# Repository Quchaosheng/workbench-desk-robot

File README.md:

# Workbench Desk Robot

> **Verify before you say done.**
>
> An evidence-first foundation for mobile domestic robots: bounded actions,
> replayable events, and a verifier that can say **confirmed**, **refuted**, or
> **insufficient evidence**.

[简体中文](README.zh-CN.md) · [Interactive 3D view](docs/assets/premium-product-render.html)

## Why Workbench?

Robot demos often treat “command accepted” as “task complete”. Workbench keeps
the proof in the loop:

```text
goal -> bounded planner -> semantic action -> trusted executor
                                      \-> event store -> verifier -> replay/dashboard
```

| Layer | Responsibility |
| --- | --- |
| Intent | Select from a small, typed action vocabulary |
| Execution | Dispatch through trusted runtime code |
| Verification | Check post-action evidence; never guess success |
| Replay | Rebuild the state from an append-only event stream |

## Quickstart

Requirements: Python 3.12. No GPU is required for the offline runtime.

```bash
git clone https://github.com/Quchaosheng/workbench-desk-robot.git
cd workbench-desk-robot
python -m pip install -e ".[dev]"
python tools/scripts/sim_cli.py doctor
python tools/scripts/sim_cli.py run normal-001 --runner scripted --output-dir runs/demo
```

Run the full portable checks:

```bash
python -m pytest -q
python -m ruff check .
```

The scripted runner writes a replayable artifact (manifest, scene, events,
logs, metadata, and SHA-256 checksums) labelled `SCRIPTED_FIXTURE`.

## What is included

- Evidence-first verification with `confirmed`, `refuted`, and `insufficient_evidence`.
- Strict JSON schemas and matching Pydantic contracts.
- Append-only SQLite event storage with integrity-checked replay.
- Fail-closed policy validation for bounded semantic tools.
- Read-only dashboard and deterministic simulation fixtures.
- Software-only foundations for MCU, CAN, Motion, and BSP boundaries.

## Optional: OmniLink knowledge layer

[OmniLink AI](https://github.com/vivekmaru/omnilink-ai) is an independent service
for searching maintenance notes, ADRs, issues, and Workbench run summaries. It
is not a planner, executor, verifier, or robot-control dependency.

```bash
git clone https://github.com/vivekmaru/omnilink-ai.git
cd omnilink-ai
npm install
npm run dev                 # normally http://127.0.0.1:3000
```

Workbench uses the standard-library adapter in [`integrations/omnilink/`](integrations/omnilink/):

```python
from integrations.omnilink import OmniLinkClient

client = OmniLinkClient("http://127.0.0.1:3000")
results = client.search("gripper calibration")
answer = client.ask("Which calibration notes mention the gripper?")
```

Only bounded run summaries are exportable. Raw JSONL, `TaskGraph`,
`SemanticAction`, action results, camera data, and safety state stay in
Workbench. Catch `OmniLinkError` so an unavailable knowledge service cannot
block offline operation. See the [integration guide](integrations/omnilink/README.md)
for deployment and security requirements.

## Honest status

The offline runtime and software boundaries are tested. End-to-end Gazebo worlds,
real perception, semantic motion execution, and physical hardware evidence are
not yet release claims. See [`docs/architecture/`](docs/architecture/) and
[`sim/README.md`](sim/README.md) for the current evidence boundary.

## Documentation

- [User guide](docs/user-guide/index.md)
- [Product evidence layer](docs/product/README.md)
- [System architecture](docs/architecture/system.md)
- [Simulation boundary](sim/README.md)
- [Motion foundation](robot/control/README.md)
- [Safety MCU](firmware/mcu/README.md)
- [Robot BSP](bsp/README.md)
- [Deployment](docs/deployment/multi-host.md)
- [Security policy](SECURITY.md)

## License

Apache-2.0. See [LICENSE](LICENSE).

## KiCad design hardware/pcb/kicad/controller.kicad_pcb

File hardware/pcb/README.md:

# Controller PCB engineering package

Eight-layer controller/power-distribution board for a 48 V desk robot. The package
defines the electrical architecture, interfaces, protection, isolated CAN,
stackup, placement/thermal constraints, DFM limits, and manufacturing outputs.

## Reproduce checks

```bash
python hardware/pcb/tools/electrical_checks.py
```

The report is written to `generated/electrical_report.json`. Open
`kicad/controller.kicad_pro` with KiCad 10. The detailed EVT companion board has
110 controlled electrical components, four M3 NPTH mounting holes (114 total
footprints), eight SMT test pads, 1,250 track/via items, 30 filled copper zones,
eight copper layers, and a physical 8 mm primary/secondary isolation region.
Reproduce the controlled sources with:

```bash
<kicad>/bin/python hardware/pcb/tools/generate_footprints.py
python hardware/pcb/tools/generate_kicad_schematic.py
python hardware/pcb/tools/generate_expected_connectivity.py
python hardware/pcb/tools/generate_bom.py
<kicad>/bin/python hardware/pcb/tools/generate_kicad_board.py --session hardware/pcb/kicad/controller.ses
python hardware/pcb/tools/electrical_checks.py
python hardware/pcb/tools/audit_connectivity.py
python hardware/pcb/tools/layout_audit.py
python hardware/pcb/tools/export_fabrication.py
python hardware/pcb/tools/release_readiness.py
```

`kicad/controller.ses` is the checked Freerouting 2.3.0 routing session. The
board generator validates every footprint position against that session before
importing 1,039 routed segments and 137 vias. Deterministic cleanup and local
supplements produce the final 1,070 segments, 180 vias, and 30 copper zones. A
stale session cannot silently attach to moved footprints.

The layout audit hard-gates the current U2 `12V_ISO` source and `GND` return with
separate eight-via rings on 3 x 3, 1.5 mm-pitch grids around the THT pads. These
rings are a spatial and current-path concept check only: U2 remains
`TBD_36_60V_TO_12V_240W_ISOLATED`, with no frozen MPN or land pattern. The
selected converter requires an ECO that replaces the footprint and placement,
rebuilds routing and planes, reruns DRC/connectivity, and repeats the thermal
review. The audit also requires top-layer, zero-via
oscillator routing, matched CAN via counts, and an `In1.Cu` `GND_CAN_ISO` zone
declaration. U7 has an all-eight-layer no-track/no-via/no-pour corridor across
its 5.87 mm board pad gap; this preserves the available geometry but does not
repair the candidate module's 2 mm creepage/clearance or 200 Vrms working rating.
CAN coupling, branch/stub geometry, reference-plane continuity, and
120 ohm field solving remain explicit manual or supplier risks rather than being
inferred from aggregate route lengths.

Test access is separated by electrical domain: TP1 remains in the 48 V primary
region, TP2-TP5/TP8 are on the logic side, and TP6/TP7 sit beside the isolated
CAN connectors. This keeps secondary probes out of the primary test area and
avoids long CAN test stubs.

The checked-in ERC and DRC reports contain zero violations and zero unconnected
items. Gerbers, drills, IPC-D-356, position data, drawings, statistics, and a
rendered inspection preview are under `fabrication/`.
`kicad/controller.kicad_dru` enforces 8 mm copper clearance between the primary
48 V domain and every non-primary net; release readiness fails if this rule is
missing even when the base DRC report is otherwise clean.

## Critical design-review correction

The original task suggestion (`TPS54160 + RT8059 + AMS1117`) is not load-capable:

- TPS54160 is a 1.5 A regulator and cannot supply the proposed 12 V motor rail.
- RT8059 is a low-current converter and cannot supply a 5 V / 8 A Jetson rail.
- AMS1117 cannot provide 3.3 V / 5 A and would exceed its thermal limit.

The baseline therefore requires a protected 48 V input and an isolated,
regulated 36-60 V-to-12 V 240 W-class module, followed by a protected 12 V / 5 A
branch to the Jetson developer-kit DC
input, and a 12-to-3.3 V 20 W synchronous buck. It deliberately does not
back-power the developer kit through a 5 V header. Design candidates are listed
in the fabrication BOM; purchase
requires the system owner's AVL sign-off because component selection is outside
issue #19's ownership boundary.

U2 has no orderable design candidate. `DCM3623T50M31C2T00` is explicitly excluded: the
official Vicor PDF specifies 16-50 V input, 28 V output, and a nine-terminal
through-hole ChiP package, so it cannot meet the 36-60 V-to-12 V requirement and
its land pattern is incompatible with the checked layout. The Vicor source in
`source-baseline.json` is exclusion evidence only. Until a real MPN and vendor
land pattern are frozen, the checked schematic, BOM, PCB and routing session use
a consistent `NOT FOR PRODUCTION` placeholder that must not be assembled or ordered.

The board is a companion/control board for the NVIDIA developer kit, not a raw
260-pin Jetson module carrier. See `interface-control.md` and
`source-baseline.json` for controlled interfaces, official sources, assumptions,
owners, and freeze gates. J4 is populated on this board; J7-J9 describe downstream
harness or daughterboard endpoints and are not populated in revision A.
The ISO1042 bus side uses distinct `5V_CAN_ISO` and `GND_CAN_ISO` nets supplied
by U7; neither is tied to logic ground in the board database.
The populated J4 backplane carries the external `JETSON_ENABLE_REQ` on pin 8;
it is an MCU input and is deliberately distinct from the internal
`MOTOR_ENABLE_REQ` generated on U5 pin 53. The E-stop path has distinct
`MOTOR_ENABLE_REQ` and `MOTOR_ENABLE_SAFE` nets,
a dual-channel J10 loop, dual-channel manual reset at J12, diagnostic isolation
at U8, force-guided relay candidates K1/K2, and the J11 gated output.
`connector-pinout.csv` freezes the current EVT pin mapping.
`connectors.csv` separates contact capability from the controlled system
envelope: J2 contacts are a 16 A nominal interface, but the board and harness
are limited to 10 A aggregate (120 W at 12 V) until an external branch fuse,
inrush, regeneration and fault-current analysis is approved.
`component-selection-matrix.csv` tracks every active module, the source-backed
candidate or class, verification method, owner and procurement status.
`fabrication/bom.csv` contains 77 grouped lines covering every board component.
`component-approval-register.csv` contains owner and evidence slots for every
one of the 68 procurement-controlled groups; no row is treated as approved without a named MPN,
datasheet revision, approver, date, and evidence reference.
Changing `decision` to `APPROVED` is insufficient: an orderable MPN, datasheet
revision, named approver, date, and evidence reference are all required.
`expected-connectivity.json` and `generated/connectivity_report.json` independently
check 458 physical pads across all 110 controlled components, plus input-protection, CAN
isolation, current-sense and dual-channel safety invariants.
`testpoint-coverage.csv` defines the measurement, limit, instrument and required
evidence for every physical test pad.

Run `python hardware/pcb/tools/release_readiness.py` before sharing an order
package. The checked-in schematic is component-level (110 symbols and 366 wired
net labels) and has clean ERC. Order release still remains blocked until AVL,
physical bring-up, safety analysis, harness release and supplier DFM gates close.
The release audit also fails closed if the excluded U2 MPN or footprint appears
in any controlled schematic, PCB, library, routing, netlist, BOM or position
artifact, and it keeps
`isolated_power_mpn_and_land_pattern_frozen` false until the required ECO is
complete.
Do not order a populated board from engineering completeness alone.

## Release status

PCB1-11 have reproducible engineering evidence. PCB12-18 have complete order,
bring-up, reliability, and production procedures but still require physical boards,
lab instruments, EMC facilities, and production operators; see the verification
matrix for the evidence that must be attached rather than inferred.

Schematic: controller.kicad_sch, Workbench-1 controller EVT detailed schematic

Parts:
C1: 1uF 100V; C_1210_3225Metric
C2: 10uF 100V; C_2220_5750Metric
C3: 470uF 25V; CP_Radial_D12.5mm_P5.00mm
C4: 1uF 25V; C_0805_2012Metric
C5: 220uF 25V; CP_Radial_D10.0mm_P5.00mm
C6: 22uF 25V; C_1210_3225Metric
C7, C8: 47uF 10V; C_1210_3225Metric
C9, C10, C11, C12, C13, C14, C15, C16, C18, C19, C40, C41, C44: 100nF; C_0603_1608Metric
C17, C42, C43: 4.7uF; C_0805_2012Metric
C20: 1uF 10V; C_0603_1608Metric
CG1: 4.7nF 100V; C_0603_1608Metric
CSS4: 22nF; C_0603_1608Metric
CY1, CY2: 18pF; C_0603_1608Metric
D1: SMCJ58A; D_SMC; MPN Littelfuse SMCJ58A
D2: CAN FD TVS; CAN_TVS; MPN Nexperia PESD2CANFD24V-T
D3, D4: FLYBACK; D_SOD-123; MPN Diodes Inc. 1N4148W-7-F
F1: 10A 125V; Fuse_4510; MPN Littelfuse 0451010.MRL
F2: PTC 0.25A; Fuse_1206_3216Metric; MPN Littelfuse 1206L025YR
J1: 48V INPUT; MicroFit_2x2; MPN Molex 43045-0412
J2: 12V MOTOR AUX; MicroFit_2x2; MPN Molex 43045-0412
J3: JETSON DEVKIT 12V; MicroFit_2x2; MPN Molex 43045-0412
J4: JETSON MCU BACKPLANE; PinHeader_2x10_P2.54mm_Vertical
J5: CAN A; MicroFit_2x2; MPN Molex 43045-0412
J6: CAN B; MicroFit_2x2; MPN Molex 43045-0412
J10: DUAL ESTOP LOOP; MicroFit_2x2; MPN Molex 43045-0412
J11: SAFETY OUTPUT; MicroFit_2x2; MPN Molex 43045-0412
J12: DUAL MANUAL RESET; MicroFit_2x2; MPN Molex 43045-0412
J13: WCH DEBUG; PinHeader_1x04_P2.54mm_Vertical
JP1: CAN TERM; PinHeader_1x02_P2.54mm_Vertical
K1: FORCE-GUIDED 12V A; Panasonic_SFM4; MPN Panasonic SFM4-DC12V
K2: FORCE-GUIDED 12V B; Panasonic_SFM4; MPN Panasonic SFM4-DC12V
L1: 100R@100MHz; ACT45B; MPN TDK ACT45B-101-2P-TL003
Q1, Q2: 150V N-MOS; Infineon_PG-TDSON-8_6.15x5.15mm; MPN Infineon BSC093N15NS5ATMA1
R30, R31, R32, R33, R34, R35, R36, R37, R38, R39, R40, R41, R42: 33R; R_0603_1608Metric
R43, R44, R45, R46, R57: 100k; R_0603_1608Metric
R47, R49, R50, R51, R54: 10k; R_0603_1608Metric
R48: 3.00k 1%; R_0603_1608Metric
R52, R53, R55, R56: 4.7k; R_0603_1608Metric
R58: 120R 1%; R_1206_3216Metric
R59: 73.2k 1%; R_0603_1608Metric
R60: 10.0k 1%; R_0603_1608Metric
RFB1: 45.0k 1%; R_0603_1608Metric
RFB2: 10.0k 1%; R_0603_1608Metric
RG1: 22k; R_0603_1608Metric
RPG1: 453k 1%; R_0603_1608Metric
RPG2: 56.0k 1%; R_0603_1608Metric
RPG3: 10k; R_0603_1608Metric
RS1: 6mR 3W 1%; Sense_3637; MPN Vishay WSL3637R0060FEA
RSH1: 510k; R_0603_1608Metric
RUV1: 19.6M 1%; R_1206_3216Metric
RUV2: 133k 1%; R_0603_1608Metric
RUV3: 162k 1%; R_0603_1608Metric
TP1: VBAT_PROTECTED; TestPoint_Pad_D1.5mm
TP2: 12V_ISO; TestPoint_Pad_D1.5mm
TP3: JETSON_12V; TestPoint_Pad_D1.5mm
TP4: 3V3_LOGIC; TestPoint_Pad_D1.5mm
TP5: GND; TestPoint_Pad_D1.5mm
TP6: CANH; TestPoint_Pad_D1.5mm
TP7: CANL; TestPoint_Pad_D1.5mm
TP8: MCU_RESET; TestPoint_Pad_D1.5mm
U1: LTC4368HMS-2; MSOP-10_3x3mm_P0.5mm; MPN LTC4368HMS-2#PBF
U2: ISOLATED 48V-12V 240W (TBD); Isolated_48V_12V_240W_TBD; MPN TBD_36_60V_TO_12V_240W_ISOLATED; not fitted
U3: TPS26633RGE; TPS26633_RGE24; MPN Texas Instruments TPS26633RGER
U4: RPL-5.0 3V3/5A; RPL-5.0_QFN24; MPN RECOM RPL-5.0-R
U5: CH32V307VCT6; LQFP-100_14x14mm_P0.5mm; MPN WCH CH32V307VCT6
U6: ISO1042DW; ISO1042_DW16_HV; MPN Texas Instruments ISO1042DWR
U7: 3V3-5V ISO 1W; Converter_DCDC_muRata_MEJ1SxxxxSC_THT; MPN Murata MEJ1S0305SC
U8: ESTOP DIAGNOSTIC OPTO; SOIC-16W_7.5x10.3mm_P1.27mm; MPN Toshiba TLP293-4(GB,E)
Y1: 8MHz; Crystal_SMD_3225-4Pin_3.2x2.5mm; MPN Abracon ABM8-8.000MHZ-B2-T

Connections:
3V3_LOGIC: C7.1 (+), C8.1 (+), C9.1 (+), C10.1 (+), C11.1 (+), C12.1 (+), C13.1 (+), C14.1 (+), C15.1 (+), C16.1 (+), C17.1 (+), C40.1 (+), C42.1 (+), J4.1, J4.3, J11.4, J13.1, K1.5 (SENSE_COM), K1.9 (EDM_COM), K2.9 (EDM_COM), R47.1, R49.1, R50.1, R54.1, R55.1, R56.1, RFB1.1, RPG3.1, TP4.1, U3.12 (SHDN), U4.9 (VOUT), U4.10 (VOUT), U4.11 (VOUT), U4.12 (VOUT), U5.6 (VBAT), U5.11 (VDD), U5.21 (VREF+), U5.22 (VDDA), U5.28 (VDD), U5.50 (VIO), U5.75 (VDD), U5.100 (VIO), U6.1 (VCC1), U7.1 (+VIN)
3V3_PGOOD: U4.20 (PG), U4.21 (PG)
5V_CAN_ISO: C41.1 (+), C43.1 (+), C44.1 (+), U6.11 (VCC2), U6.16 (VCC2), U7.7 (+VOUT)
12V_ISO: C3.1 (+), C4.1 (+), C6.1 (+), F2.1 (IN), J2.1, J2.2, R46.1, R59.1, TP2.1, U2.4 (+OUT), U3.1 (IN), U3.2 (IN), U3.5 (IN_SYS), U4.22 (VIN)
BOOT0: R43.1, U5.94 (BOOT0)
CANH: D2.1 (CANH), J5.1, J6.1, L1.4 (CANH_OUT), R58.1, TP6.1
CANH_RAW: L1.1 (CANH_IN), U6.13 (CANH)
CANL: D2.2 (CANL), J5.2, J6.2, JP1.2, L1.3 (CANL_OUT), TP7.1
CANL_RAW: L1.2 (CANL_IN), U6.12 (CANL)
CAN_RX: U5.81 (PD0/CAN1_RX), U6.5 (RXD)
CAN_TERM: JP1.1, R58.2
CAN_TX: U5.82 (PD1/CAN1_TX), U6.3 (TXD)
ESTOP_12V: F2.2 (OUT), J10.1, J10.3
ESTOP_A_MON: R49.2, U5.57 (PD10), U8.16 (C1)
ESTOP_B_MON: R50.2, U5.58 (PD11), U8.14 (C2)
ESTOP_CH_A_RETURN: J10.2, J12.1, K1.7 (HOLD_COM), U8.1 (A1)
ESTOP_CH_B_RETURN: J10.4, J12.3, K2.7 (HOLD_COM), U8.3 (A2)
ESTOP_SENSE: J4.17, J11.2, K2.6 (SENSE_NO), R57.1, U5.54 (PB15)
GND: C3.2 (-), C4.2 (-), C5.2 (-), C6.2 (-), C7.2 (-), C8.2 (-), C9.2 (-), C10.2 (-), C11.2 (-), C12.2 (-), C13.2 (-), C14.2 (-), C15.2 (-), C16.2 (-), C17.2 (-), C18.2 (-), C19.2 (-), C20.2 (-), C40.2 (-), C42.2 (-), CSS4.2 (-), CY1.2 (-), CY2.2 (-), D3.2 (A), D4.2 (A), J2.3, J2.4, J3.3, J3.4, J4.2, J4.4, J11.3, J13.4, K1.2 (COIL-), K2.2 (COIL-), R43.2, R44.2, R45.2, R48.2, R51.2, R52.2, R53.2, R57.2, R60.2, RFB2.2, RPG2.2, TP5.1, U2.5 (-OUT), U3.7 (PLIM), U3.8 (GND), U3.25 (PowerPAD), U4.1 (PGND), U4.2 (PGND), U4.3 (PGND), U4.4 (PGND), U4.5 (PGND), U4.18 (AGND), U4.24 (PGND), U5.10 (VSS), U5.19 (VSSA), U5.20 (VREF-), U5.27 (VSS), U5.49 (VSS), U5.74 (VSS), U5.99 (VSS), U6.2 (GND1), U6.8 (GND1), U7.2 (-VIN), U8.13 (E2), U8.15 (E1)
GND_CAN_ISO: C41.2 (-), C43.2 (-), C44.2 (-), D2.3 (GND), D2.4 (GND), J5.3, J6.3, U6.9 (GND2), U6.10 (GND2), U6.15 (GND2), U7.5 (-VOUT)
GND_PWR: C1.2 (-), C2.2 (-), D1.2 (A), J1.3, J1.4, RUV3.2, U1.1 (GND), U1.2 (RETRY), U2.2 (-IN)
I2C_SCL: J4.16, R39.2, R55.2
I2C_SCL_MCU: R39.1, U5.92 (PB6/I2C1_SCL)
I2C_SDA: J4.15, R40.2, R56.2
I2C_SDA_MCU: R40.1, U5.93 (PB7/I2C1_SDA)
JETSON_12V: C5.1 (+), J3.1, J3.2, RPG1.1, TP3.1, U3.17 (OUT), U3.18 (OUT)
JETSON_ENABLE_REQ: J4.8, U5.91 (PB5)
JETSON_FAULT_N: R47.2, U3.14 (FLT)
JETSON_PGOOD: RPG3.2, U3.16 (PGOOD)
MCU_RESET: C19.1 (+), J4.20, R54.2, TP8.1, U5.14 (NRST)
MOTOR_CS0: J4.9, R33.2
MOTOR_CS0_MCU: R33.1, U5.35 (PB0)
MOTOR_CS1: J4.10, R34.2
MOTOR_CS1_MCU: R34.1, U5.36 (PB1)
MOTOR_CS2: J4.11, R35.2
MOTOR_CS2_MCU: R35.1, U5.47 (PB10)
MOTOR_CS3: J4.12, R36.2
MOTOR_CS3_MCU: R36.1, U5.48 (PB11)
MOTOR_CS4: J4.13, R37.2
MOTOR_CS4_MCU: R37.1, U5.51 (PB12)
MOTOR_CS5: J4.14, R38.2
MOTOR_CS5_MCU: R38.1, U5.52 (PB13)
MOTOR_ENABLE_REQ: K1.3 (SAFE_COM), U5.53 (PB14)
MOTOR_ENABLE_SAFE: J11.1, K2.4 (SAFE_NO)
OSC_IN: CY1.1 (+), U5.12 (OSC_IN), Y1.1
OSC_OUT: CY2.1 (+), U5.13 (OSC_OUT), Y1.2
OV_SET: RUV2.2, RUV3.1, U1.3 (OV)
RELAY_A_NC: K1.10 (EDM_NC), R44.1, U5.55 (PD8)
RELAY_B_NC: K2.10 (EDM_NC), R45.1, U5.56 (PD9)
RESET_CH_A_RETURN: D3.1 (K), J12.2, K1.1 (COIL+), K1.8 (HOLD_NO)
RESET_CH_B_RETURN: D4.1 (K), J12.4, K2.1 (COIL+), K2.8 (HOLD_NO)
SAFE_STAGE_A: K1.4 (SAFE_NO), K2.3 (SAFE_COM)
SENSE_STAGE_A: K1.6 (SENSE_NO), K2.5 (SENSE_COM)
SPI_MISO: J4.7, R32.2
SPI_MISO_MCU: R32.1, U5.31 (PA6/SPI1_MISO)
SPI_MOSI: J4.6, R31.2
SPI_MOSI_MCU: R31.1, U5.32 (PA7/SPI1_MOSI)
SPI_SCLK: J4.5, R30.2
SPI_SCLK_MCU: R30.1, U5.30 (PA5/SPI1_SCK)
SWCLK: J13.3, U5.76 (SWCLK)
SWDIO: J13.2, U5.72 (SWDIO)
U1_GATE: RG1.1, U1.10 (GATE)
U1_SHDN: RSH1.2, U1.6 (SHDN)
U3_DVDT: C18.1 (+), U3.9 (dVdT)
U3_ILIM: R48.1, U3.10 (ILIM)
U3_IMON: R51.1, U3.13 (IMON)
U3_PGTH: RPG1.2, RPG2.1, U3.15 (PGTH)
U3_UVLO: R59.2, R60.1, U3.6 (UVLO)
U4_CTRL: R46.2, U4.16 (CTRL)
U4_FB: RFB1.2, RFB2.1, U4.17 (FB)
U4_SS: CSS4.1 (+), U4.19 (SS)
U4_VCC: C20.1 (+), U4.6 (VCC)
U8_LED_A_K: R52.1, U8.2 (K1)
U8_LED_B_K: R53.1, U8.4 (K2)
UART_RX: J4.19, R42.2
UART_RX_MCU: R42.1, U5.69 (PA10/USART1_RX)
UART_TX: J4.18, R41.2
UART_TX_MCU: R41.1, U5.68 (PA9/USART1_TX)
UV_SET: RUV1.2, RUV2.1, U1.4 (UV)
VBAT_PROTECTED: C1.1 (+), C2.1 (+), RS1.2, TP1.1, U1.8 (VOUT), U2.1 (+IN)
VBAT_RAW: F1.1 (IN), J1.1, J1.2

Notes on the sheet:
INPUT PROTECTION
ISOLATED POWER
JETSON EFUSE
3V3 POWER
POWER OUTPUTS
MCU AND BACKPLANE
ISOLATED CAN FD
HARDWIRED ESTOP
TEST ACCESS

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
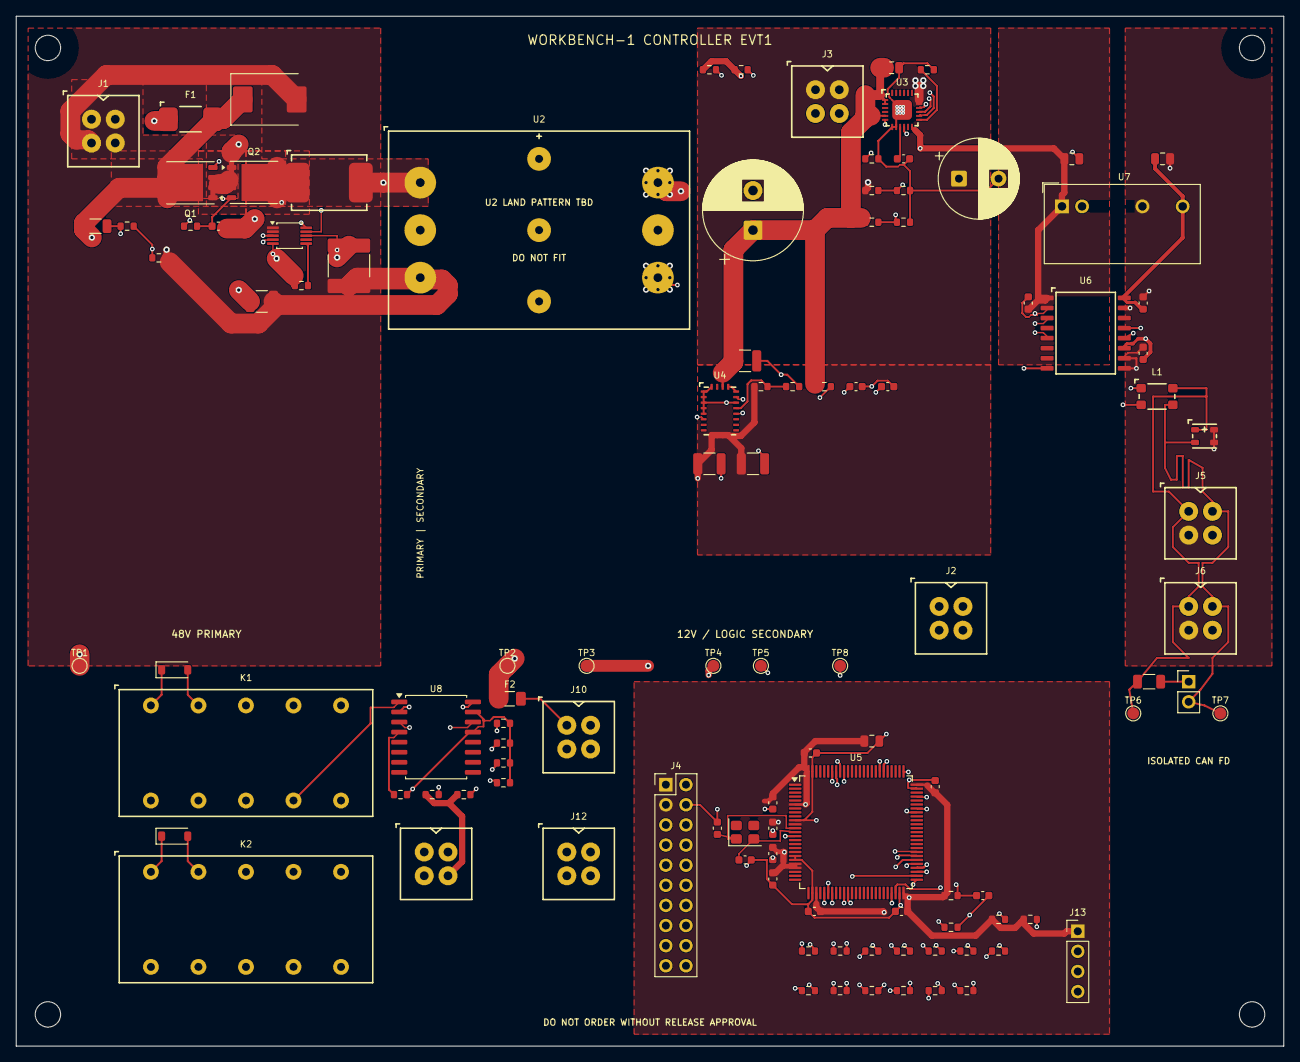
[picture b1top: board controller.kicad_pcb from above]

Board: 8 copper layers, 160.0 x 130.0 mm, 114 parts (0 on the bottom side), 85 nets.

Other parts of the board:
H1, H2, H3, H4: M3_NPTH

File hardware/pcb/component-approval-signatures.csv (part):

reference,candidate,role,decision,signed_by,signed_at,evidence_ref,hardware_revision,bom_sha256
C1,1uF 100V; Capacitor_SMD:C_1210_3225Metric,Electrical Owner,PENDING,,,,EVT1,8bd6e5783d06f4d9843280ec2a9fefa463ba92380c1dc87a954b52f28e142c0f
C1,1uF 100V; Capacitor_SMD:C_1210_3225Metric,Procurement Owner,PENDING,,,,EVT1,8bd6e5783d06f4d9843280ec2a9fefa463ba92380c1dc87a954b52f28e142c0f
C2,10uF 100V; Capacitor_SMD:C_2220_5750Metric,Electrical Owner,PENDING,,,,EVT1,8bd6e5783d06f4d9843280ec2a9fefa463ba92380c1dc87a954b52f28e142c0f
C2,10uF 100V; Capacitor_SMD:C_2220_5750Metric,Procurement Owner,PENDING,,,,EVT1,8bd6e5783d06f4d9843280ec2a9fefa463ba92380c1dc87a954b52f28e142c0f
C3,470uF 25V; Capacitor_THT:CP_Radial_D12.5mm_P5.00mm,Electrical Owner,PENDING,,,,EVT1,8bd6e5783d06f4d9843280ec2a9fefa463ba92380c1dc87a954b52f28e142c0f
C3,470uF 25V; Capacitor_THT:CP_Radial_D12.5mm_P5.00mm,Procurement Owner,PENDING,,,,EVT1,8bd6e5783d06f4d9843280ec2a9fefa463ba92380c1dc87a954b52f28e142c0f
C4,1uF 25V; Capacitor_SMD:C_0805_2012Metric,Electrical Owner,PENDING,,,,EVT1,8bd6e5783d06f4d9843280ec2a9fefa463ba92380c1dc87a954b52f28e142c0f
C4,1uF 25V; Capacitor_SMD:C_0805_2012Metric,Procurement Owner,PENDING,,,,EVT1,8bd6e5783d06f4d9843280ec2a9fefa463ba92380c1dc87a954b52f28e142c0f
C5,220uF 25V; Capacitor_THT:CP_Radial_D10.0mm_P5.00mm,Electrical Owner,PENDING,,,,EVT1,8bd6e5783d06f4d9843280ec2a9fefa463ba92380c1dc87a954b52f28e142c0f
C5,220uF 25V; Capacitor_THT:CP_Radial_D10.0mm_P5.00mm,Procurement Owner,PENDING,,,,EVT1,8bd6e5783d06f4d9843280ec2a9fefa463ba92380c1dc87a954b52f28e142c0f
C6,22uF 25V; Capacitor_SMD:C_1210_3225Metric,Electrical Owner,PENDING,,,,EVT1,8bd6e5783d06f4d9843280ec2a9fefa463ba92380c1dc87a954b52f28e142c0f
C6,22uF 25V; Capacitor_SMD:C_1210_3225Metric,Procurement Owner,PENDING,,,,EVT1,8bd6e5783d06f4d9843280ec2a9fefa463ba92380c1dc87a954b52f28e142c0f
C7 C8,47uF 10V; Capacitor_SMD:C_1210_3225Metric,Electrical Owner,PENDING,,,,EVT1,8bd6e5783d06f4d9843280ec2a9fefa463ba92380c1dc87a954b52f28e142c0f
C7 C8,47uF 10V; Capacitor_SMD:C_1210_3225Metric,Procurement Owner,PENDING,,,,EVT1,8bd6e5783d06f4d9843280ec2a9fefa463ba92380c1dc87a954b52f28e142c0f
C9 C10 C11 C12 C13 C14 C15 C16 C19,100nF; Capacitor_SMD:C_0603_1608Metric,Firmware Owner,PENDING,,,,EVT1,8bd6e5783d06f4d9843280ec2a9fefa463ba92380c1dc87a954b52f28e142c0f
C9 C10 C11 C12 C13 C14 C15 C16 C19,100nF; Capacitor_SMD:C_0603_1608Metric,Electrical Owner,PENDING,,,,EVT1,8bd6e5783d06f4d9843280ec2a9fefa463ba92380c1dc87a954b52f28e142c0f
C9 C10 C11 C12 C13 C14 C15 C16 C19,100nF; Capacitor_SMD:C_0603_1608Metric,Procurement Owner,PENDING,,,,EVT1,8bd6e5783d06f4d9843280ec2a9fefa463ba92380c1dc87a954b52f28e142c0f
C17,4.7uF; Capacitor_SMD:C_0805_2012Metric,Firmware Owner,PENDING,,,,EVT1,8bd6e5783d06f4d9843280ec2a9fefa463ba92380c1dc87a954b52f28e142c0f
C17,4.7uF; Capacitor_SMD:C_0805_2012Metric,Electrical Owner,PENDING,,,,EVT1,8bd6e5783d06f4d9843280ec2a9fefa463ba92380c1dc87a954b52f28e142c0f
C17,4.7uF; Capacitor_SMD:C_0805_2012Metric,Procurement Owner,PENDING,,,,EVT1,8bd6e5783d06f4d9843280ec2a9fefa463ba92380c1dc87a954b52f28e142c0f
C18,100nF; Capacitor_SMD:C_0603_1608Metric,Electrical Owner,PENDING,,,,EVT1,8bd6e5783d06f4d9843280ec2a9fefa463ba92380c1dc87a954b52f28e142c0f
C18,100nF; Capacitor_SMD:C_0603_1608Metric,Procurement Owner,PENDING,,,,EVT1,8bd6e5783d06f4d9843280ec2a9fefa463ba92380c1dc87a954b52f28e142c0f
C20,1uF 10V; Capacitor_SMD:C_0603_1608Metric,Electrical Owner,PENDING,,,,EVT1,8bd6e5783d06f4d9843280ec2a9fefa463ba92380c1dc87a954b52f28e142c0f
C20,1uF 10V; Capacitor_SMD:C_0603_1608Metric,Procurement Owner,PENDING,,,,EVT1,8bd6e5783d06f4d9843280ec2a9fefa463ba92380c1dc87a954b52f28e142c0f
C40 C41 C44,100nF; Capacitor_SMD:C_0603_1608Metric,Electrical Owner,PENDING,,,,EVT1,8bd6e5783d06f4d9843280ec2a9fefa463ba92380c1dc87a954b52f28e142c0f
C40 C41 C44,100nF; Capacitor_SMD:C_0603_1608Metric,Procurement Owner,PENDING,,,,EVT1,8bd6e5783d06f4d9843280ec2a9fefa463ba92380c1dc87a954b52f28e142c0f
C42 C43,4.7uF; Capacitor_SMD:C_0805_2012Metric,Electrical Owner,PENDING,,,,EVT1,8bd6e5783d06f4d9843280ec2a9fefa463ba92380c1dc87a954b52f28e142c0f
C42 C43,4.7uF; Capacitor_SMD:C_0805_2012Metric,Procurement Owner,PENDING,,,,EVT1,8bd6e5783d06f4d9843280ec2a9fefa463ba92380c1dc87a954b52f28e142c0f
CG1,4.7nF 100V; Capacitor_SMD:C_0603_1608Metric,Electrical Owner,PENDING,,,,EVT1,8bd6e5783d06f4d9843280ec2a9fefa463ba92380c1dc87a954b52f28e142c0f
CG1,4.7nF 100V; Capacitor_SMD:C_0603_1608Metric,Procurement Owner,PENDING,,,,EVT1,8bd6e5783d06f4d9843280ec2a9fefa463ba92380c1dc87a954b52f28e142c0f
CSS4,22nF; Capacitor_SMD:C_0603_1608Metric,Electrical Owner,PENDING,,,,EVT1,8bd6e5783d06f4d9843280ec2a9fefa463ba92380c1dc87a954b52f28e142c0f
CSS4,22nF; Capacitor_SMD:C_0603_1608Metric,Procurement Owner,PENDING,,,,EVT1,8bd6e5783d06f4d9843280ec2a9fefa463ba92380c1dc87a954b52f28e142c0f
CY1 CY2,18pF; Capacitor_SMD:C_0603_1608Metric,Firmware Owner,PENDING,,,,EVT1,8bd6e5783d06f4d9843280ec2a9fefa463ba92380c1dc87a954b52f28e142c0f
CY1 CY2,18pF; Capacitor_SMD:C_0603_1608Metric,Electrical Owner,PENDING,,,,EVT1,8bd6e5783d06f4d9843280ec2a9fefa463ba92380c1dc87a954b52f28e142c0f
CY1 CY2,18pF; Capacitor_SMD:C_0603_1608Metric,Procurement Owner,PENDING,,,,EVT1,8bd6e5783d06f4d9843280ec2a9fefa463ba92380c1dc87a954b52f28e142c0f
D1,Littelfuse SMCJ58A,Electrical Owner,PENDING,,,,EVT1,8bd6e5783d06f4d9843280ec2a9fefa463ba92380c1dc87a954b52f28e142c0f
D1,Littelfuse SMCJ58A,Procurement Owner,PENDING,,,,EVT1,8bd6e5783d06f4d9843280ec2a9fefa463ba92380c1dc87a954b52f28e142c0f
D2,Nexperia PESD2CANFD24V-T,Electrical Owner,PENDING,,,,EVT1,8bd6e5783d06f4d9843280ec2a9fefa463ba92380c1dc87a954b52f28e142c0f
D2,Nexperia PESD2CANFD24V-T,Procurement Owner,PENDING,,,,EVT1,8bd6e5783d06f4d9843280ec2a9fefa463ba92380c1dc87a954b52f28e142c0f
D3 D4,Diodes Inc. 1N4148W-7-F,Safety Owner,PENDING,,,,EVT1,8bd6e5783d06f4d9843280ec2a9fefa463ba92380c1dc87a954b52f28e142c0f
D3 D4,Diodes Inc. 1N4148W-7-F,Electrical Owner,PENDING,,,,EVT1,8bd6e5783d06f4d9843280ec2a9fefa463ba92380c1dc87a954b52f28e142c0f
D3 D4,Diodes Inc. 1N4148W-7-F,Procurement Owner,PENDING,,,,EVT1,8bd6e5783d06f4d9843280ec2a9fefa463ba92380c1dc87a954b52f28e142c0f
F1,Littelfuse 0451010.MRL,Electrical Owner,PENDING,,,,EVT1,8bd6e5783d06f4d9843280ec2a9fefa463ba92380c1dc87a954b52f28e142c0f
F1,Littelfuse 0451010.MRL,Procurement Owner,PENDING,,,,EVT1,8bd6e5783d06f4d9843280ec2a9fefa463ba92380c1dc87a954b52f28e142c0f
F2,Littelfuse 1206L025YR,Safety Owner,PENDING,,,,EVT1,8bd6e5783d06f4d9843280ec2a9fefa463ba92380c1dc87a954b52f28e142c0f
F2,Littelfuse 1206L025YR,Electrical Owner,PENDING,,,,EVT1,8bd6e5783d06f4d9843280ec2a9fefa463ba92380c1dc87a954b52f28e142c0f
F2,Littelfuse 1206L025YR,Procurement Owner,PENDING,,,,EVT1,8bd6e5783d06f4d9843280ec2a9fefa463ba92380c1dc87a954b52f28e142c0f
J1,Molex 43045-0412,System Owner,PENDING,,,,EVT1,8bd6e5783d06f4d9843280ec2a9fefa463ba92380c1dc87a954b52f28e142c0f
J1,Molex 43045-0412,Electrical Owner,PENDING,,,,EVT1,8bd6e5783d06f4d9843280ec2a9fefa463ba92380c1dc87a954b52f28e142c0f
J1,Molex 43045-0412,Procurement Owner,PENDING,,,,EVT1,8bd6e5783d06f4d9843280ec2a9fefa463ba92380c1dc87a954b52f28e142c0f
J2,Molex 43045-0412,Electrical Owner,PENDING,,,,EVT1,8bd6e5783d06f4d9843280ec2a9fefa463ba92380c1dc87a954b52f28e142c0f
J2,Molex 43045-0412,Procurement Owner,PENDING,,,,EVT1,8bd6e5783d06f4d9843280ec2a9fefa463ba92380c1dc87a954b52f28e142c0f
J3,Molex 43045-0412,System Owner,PENDING,,,,EVT1,8bd6e5783d06f4d9843280ec2a9fefa463ba92380c1dc87a954b52f28e142c0f
J3,Molex 43045-0412,Electrical Owner,PENDING,,,,EVT1,8bd6e5783d06f4d9843280ec2a9fefa463ba92380c1dc87a954b52f28e142c0f
J3,Molex 43045-0412,Procurement Owner,PENDING,,,,EVT1,8bd6e5783d06f4d9843280ec2a9fefa463ba92380c1dc87a954b52f28e142c0f
J4,JETSON MCU BACKPLANE; Connector_PinHeader_2.54mm:PinHeader_2x10_P2.54mm_Vertical,Firmware Owner,PENDING,,,,EVT1,8bd6e5783d06f4d9843280ec2a9fefa463ba92380c1dc87a954b52f28e142c0f
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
